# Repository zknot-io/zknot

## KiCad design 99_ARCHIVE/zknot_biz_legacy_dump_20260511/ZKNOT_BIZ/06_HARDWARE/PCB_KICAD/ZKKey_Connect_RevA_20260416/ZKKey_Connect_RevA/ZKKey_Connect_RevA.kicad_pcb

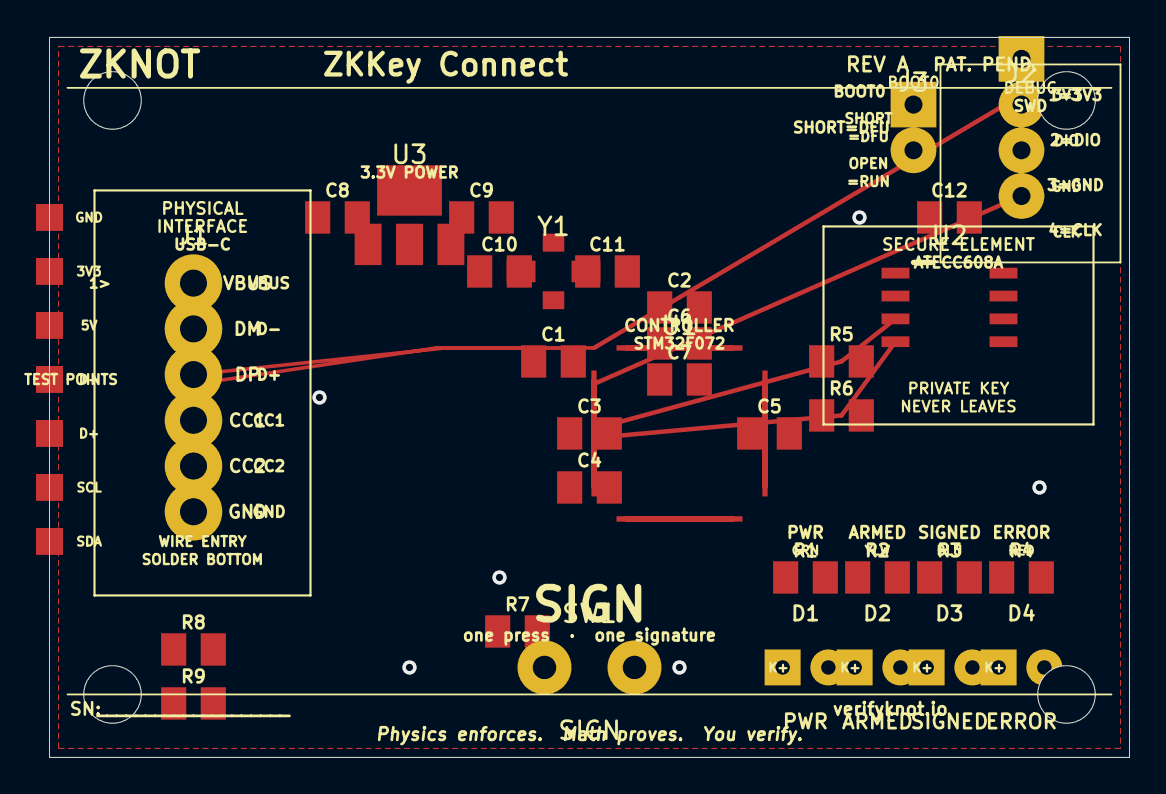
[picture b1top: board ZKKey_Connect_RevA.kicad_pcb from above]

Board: 2 copper layers, 60.0 x 40.0 mm, 33 parts (0 on the bottom side), 19 nets.

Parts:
C1, C2, C3, C4, C5, C6, C7, C8, C9, C10, C11, C12: C_0805_2012Metric
D1: PWR; LED_D3.0mm
D2: ARMED; LED_D3.0mm
D3: SIGNED; LED_D3.0mm
D4: ERROR; LED_D3.0mm
J1: USB-C_Male_Pigtail; PinHeader_1x06_P2.54mm_Vertical
J2: SWD; PinHeader_1x04_P2.54mm_Vertical
J3: BOOT0; PinHeader_1x02_P2.54mm_Vertical
R1, R2, R3, R4, R5, R6, R7, R8, R9: R_0805_2012Metric
SW1: SIGN; SW_Tactile_SPST_Angled_PTS645
U1: STM32F072CBT6; LQFP-48_7x7mm_P0.5mm
U2: ATECC608A; SOIC-8_3.9x4.9mm_P1.27mm
U3: AMS1117-3.3; SOT-223-3_TabPin2
Y1: 8MHz; Crystal_SMD_3225-4Pin_3.2x2.5mm

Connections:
+3.3V: C2.1, C3.1, C4.1, C5.1, C6.1, C7.1, C9.1, C12.1, J2.1, J3.2, R5.1, R6.1, U1.1, U1.2, U1.9, U1.24, U1.48, U2.8, U3.2
+5V: C8.1, U3.3
ATEC_ALERT_PA5: U1.5, U1.6, U1.15, U2.2
BOOT0: J3.1, U1.44
BTN_PA0: R7.1, SW1.1, U1.10
CC1_5V1K: J1.4, R8.1
CC2_5V1K: J1.5, R9.1
GND: C1.2, C2.2, C3.2, C4.2, C5.2, C6.2, C7.2, C8.2, C9.2, C10.2, C11.2, C12.2, D1.1, D2.1, D3.1, D4.1, J1.6, J2.3, R7.2, R8.2, R9.2, SW1.2, U1.8, U1.23, U1.47, U2.3, U3.1, Y1.3, Y1.4
I2C_SCL: R5.2, U1.42, U2.7
I2C_SDA: R6.2, U1.43, U2.5
LED_ARMED_PA2: D2.2, R2.1, R2.2, U1.12
LED_ERROR_PA4: D4.2, R4.1, R4.2, U1.14
LED_PWR_PA1: D1.2, R1.1, R1.2, U1.11
LED_SIGNED_PA3: D3.2, R3.1, R3.2, U1.13
NRST: C1.1, U1.7
SWCLK: J2.4, U1.37
SWDIO: J2.2, U1.34
USB_DM: J1.2, U1.32
USB_DP: J1.3, U1.33

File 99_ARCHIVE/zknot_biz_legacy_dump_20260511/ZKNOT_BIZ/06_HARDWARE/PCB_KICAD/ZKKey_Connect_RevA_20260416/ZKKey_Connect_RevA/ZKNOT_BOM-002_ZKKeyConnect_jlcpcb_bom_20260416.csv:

Comment,Designator,Footprint,LCSC Part #,Qty,Assembly,Notes
STM32F072CBT6,U1,Package_QFP:LQFP-48_7x7mm_P0.5mm,C81720,1,SMT,Reflow — core MCU native USB
ATECC608A-MAHDA-T,U2,Package_SO:SOIC-8_3.9x4.9mm_P1.27mm,C3395330,1,SMT,Reflow — secure element
AMS1117-3.3,U3,Package_TO_SOT_SMD:SOT-223-3_TabPin2,C6186,1,SMT,Reflow — 3.3V LDO
Crystal 8MHz,Y1,Crystal:Crystal_SMD_3225-4Pin_3.2x2.5mm,C9002,1,SMT,Reflow — HSE oscillator
100nF 0805,C1 C3 C4 C5 C12,Capacitor_SMD:C_0805_2012Metric,C49678,5,SMT,Decoupling — NRST/VDD/VDD_USB/ATECC
10uF 0805,C2 C8 C9,Capacitor_SMD:C_0805_2012Metric,C17024,3,SMT,Bulk decoupling — VDD/LDO in/LDO out
1uF 0805,C6,Capacitor_SMD:C_0805_2012Metric,C15849,1,SMT,VDDA bulk
10nF 0805,C7,Capacitor_SMD:C_0805_2012Metric,C57112,1,SMT,VDDA HF
12pF 0805,C10 C11,Capacitor_SMD:C_0805_2012Metric,C1557,2,SMT,Crystal load caps — verify against Y1 datasheet
270R 0805,R1 R2 R3 R4,Resistor_SMD:R_0805_2012Metric,C17630,4,SMT,LED current limit — (3.3V-2.0V)/270=4.8mA
4.7k 0805,R5 R6,Resistor_SMD:R_0805_2012Metric,C23162,2,SMT,I2C pull-ups SCL/SDA
10k 0805,R7,Resistor_SMD:R_0805_2012Metric,C17414,1,SMT,Button pull-down PA0
5.1k 0805,R8 R9,Resistor_SMD:R_0805_2012Metric,C23186,2,SMT,USB-C CC1/CC2 pull-downs — UFP identification
LED 3mm Green,D1,LED_THT:LED_D3.0mm,,1,THT,PWR indicator — source locally
LED 3mm Yellow,D2,LED_THT:LED_D3.0mm,,1,THT,ARMED indicator — source locally
LED 3mm Blue,D3,LED_THT:LED_D3.0mm,,1,THT,SIGNED indicator — source locally
LED 3mm Red,D4,LED_THT:LED_D3.0mm,,1,THT,ERROR indicator — source locally
Tactile Switch 6x6mm,SW1,Button_Switch_THT:SW_Tactile_SPST_Angled_PTS645,,1,THT,SIGN button — source locally PTS645SK43SMTR92LFS or equiv
PinHeader 1x04 2.54mm,J2,Connector_PinHeader_2.54mm:PinHeader_1x04_P2.54mm_Vertical,,1,THT,SWD debug — source locally
PinHeader 1x02 2.54mm,J3,Connector_PinHeader_2.54mm:PinHeader_1x02_P2.54mm_Vertical,,1,THT,BOOT0 jumper — source locally
Jumper shunt 2.54mm,J3_shunt,,,,THT,BOOT0 jumper shunt — keep one on board
USB-C Male Pigtail 5-wire,J1,Connector_PinHeader_2.54mm:PinHeader_1x06_P2.54mm_Vertical,,1,THT,Source: Adafruit 4831 or equiv — VBUS DM DP CC1 CC2 GND — wire through THT holes flood solder bottom
M3 Standoff Nylon 10mm,H1 H2 H3 H4,MountingHole:MountingHole_3.2mm_M3,,4,THT,Optional — for enclosure / bench mounting

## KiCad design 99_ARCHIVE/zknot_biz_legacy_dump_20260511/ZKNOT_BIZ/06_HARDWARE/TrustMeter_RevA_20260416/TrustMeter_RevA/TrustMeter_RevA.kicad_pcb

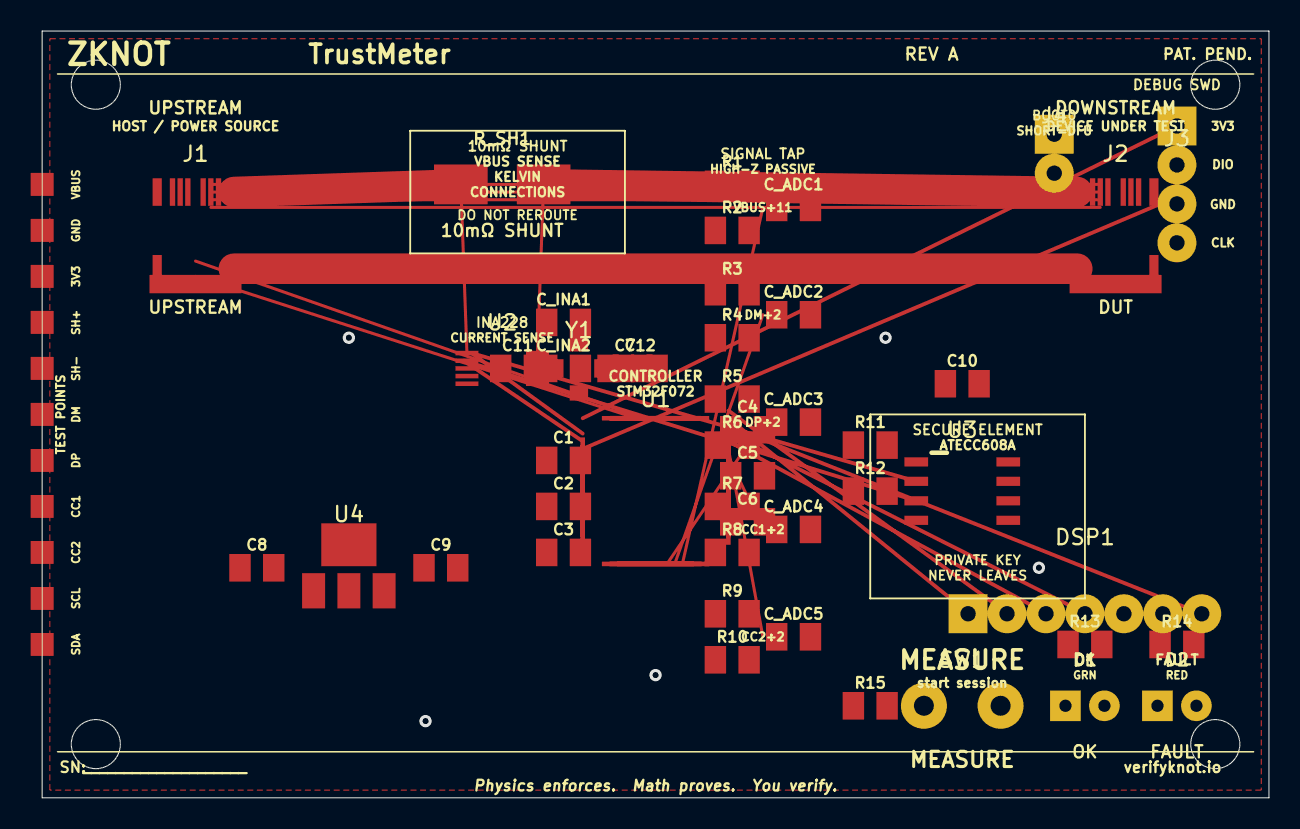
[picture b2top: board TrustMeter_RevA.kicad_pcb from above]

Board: 2 copper layers, 80.0 x 50.0 mm, 48 parts (0 on the bottom side), 31 nets.

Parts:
C1, C2, C3, C4, C5, C6, C7, C8, C9, C10, C11, C12: C_0805_2012Metric
C_ADC1, C_ADC2, C_ADC3, C_ADC4, C_ADC5: C_0805_2012Metric
C_INA1, C_INA2: C_0805_2012Metric
D1: OK; LED_D3.0mm
D2: FAULT; LED_D3.0mm
DSP1: OLED; PinHeader_1x07_P2.54mm_Vertical
J1: UPSTREAM; USB_C_Receptacle_GCT_USB4105-GF-A
J2: DUT; USB_C_Receptacle_GCT_USB4105-GF-A
J3: PinHeader_1x04_P2.54mm_Vertical
J4: PinHeader_1x02_P2.54mm_Vertical
R1, R2, R3, R4, R5, R6, R7, R8, R9, R10, R11, R12, R13, R14, R15: R_0805_2012Metric
R_SH1: 10mΩ SHUNT; R_2512_6332Metric
SW1: MEASURE; SW_Tactile_SPST_Angled_PTS645
U1: STM32F072CBT6; LQFP-48_7x7mm_P0.5mm
U2: INA228; VSSOP-10_3x3mm_P0.5mm
U3: ATECC608A; SOIC-8_3.9x4.9mm_P1.27mm
U4: AMS1117-3.3; SOT-223-3_TabPin2
Y1: Crystal_SMD_3225-4Pin_3.2x2.5mm

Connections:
+3.3V: C1.1, C2.1, C3.1, C4.1, C5.1, C6.1, C9.1, C10.1, DSP1.2, J3.1, J4.2, R11.1, R12.1, U1.1, U1.2, U1.9, U1.24, U1.48, U3.8, U4.2
+5V_VBUS_UP: J1.A4, J1.B4
ADC_CC1: C_ADC4.1, R7.2, R8.1, U1.13
ADC_CC2: C_ADC5.1, R9.2, R10.1, U1.16
ADC_DM: C_ADC2.1, R3.2, R4.1, U1.11
ADC_DP: C_ADC3.1, R5.2, R6.1, U1.12
ADC_VBUS: C_ADC1.1, R1.2, R2.1, U1.10
ATEC_ALERT: U1.39, U3.2
BOOT0: J4.1, U1.44
BTN_MEAS: R15.1, SW1.1, U1.30
CC1_UP: J1.A5, R7.1
CC2_UP: J1.B5, R9.1
DM_UP: J1.A7, R3.1
DP_UP: J1.A6, R5.1
GND: C1.2, C2.2, C3.2, C4.2, C5.2, C6.2, C7.2, C8.2, C9.2, C10.2, C11.2, C12.2, C_ADC1.2, C_ADC2.2, C_ADC3.2, C_ADC4.2, C_ADC5.2, C_INA1.2, C_INA2.2, D1.1, D2.1, DSP1.1, J1.A1, J1.B1, J1.S1, J2.A1, J2.B1, J2.S1, J3.3, R2.2, R4.2, R6.2, R8.2, R10.2, R15.2, SW1.2, U1.8, U1.23, U1.47, U2.3, U2.4, U2.5, U3.3, U4.1, Y1.3, Y1.4
I2C_SCL: R11.2, U1.42, U2.9, U3.7
I2C_SDA: R12.2, U1.43, U2.8, U3.5
INA_ALERT: U1.29, U2.7
LED_FAULT: D2.2, R14.1, R14.2, U1.22
LED_OK: D1.2, R13.1, R13.2, U1.21
NRST: C7.1, U1.7
OLED_CS: DSP1.7, U1.14
OLED_DC: DSP1.6, U1.26
OLED_RST: DSP1.5, U1.27
SPI_MOSI: DSP1.4, U1.17
SPI_SCK: DSP1.3, U1.15
SWCLK: J3.4, U1.37
SWDIO: J3.2, U1.34
VBUS_DOWN: J2.A4, J2.B4
VBUS_SHUNT_HI: R_SH1.1, U2.1
VBUS_SHUNT_LO: C8.1, C_INA1.1, C_INA2.1, R1.1, R_SH1.2, U2.2, U2.6, U2.10, U4.3

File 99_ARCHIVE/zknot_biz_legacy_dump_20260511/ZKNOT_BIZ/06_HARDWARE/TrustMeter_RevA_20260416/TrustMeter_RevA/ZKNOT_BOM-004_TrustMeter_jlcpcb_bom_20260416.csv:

Comment,Designator,Footprint,LCSC Part #,Qty,Assembly,Notes
STM32F072CBT6,U1,Package_QFP:LQFP-48_7x7mm_P0.5mm,C81720,1,SMT,Reflow — same as Connect/Air
INA228AIDGST,U2,Package_SO:VSSOP-10_3x3mm_P0.5mm,C2678360,1,SMT,Reflow — 16-bit current/voltage/power monitor I2C addr 0x40
ATECC608A-MAHDA-T,U3,Package_SO:SOIC-8_3.9x4.9mm_P1.27mm,C3395330,1,SMT,Reflow — secure element signs attestation records
AMS1117-3.3,U4,Package_TO_SOT_SMD:SOT-223-3_TabPin2,C6186,1,SMT,Reflow — 3.3V LDO from VBUS
Crystal 8MHz,Y1,Crystal:Crystal_SMD_3225-4Pin_3.2x2.5mm,C9002,1,SMT,HSE oscillator
10mΩ 1% 2W 2512,R_SH1,Resistor_SMD:R_2512_6332Metric,C17329,1,SMT,SHUNT — Kelvin connections to INA228 IN+/IN- — DO NOT SUBSTITUTE
100k 0805,R1 R3 R4 R5 R6 R7 R8 R9 R10,Resistor_SMD:R_0805_2012Metric,C17407,9,SMT,Voltage divider top+bottom for DM/DP/CC1/CC2 + VBUS top
10k 0805,R2 R15,Resistor_SMD:R_0805_2012Metric,C17414,2,SMT,VBUS divider bottom + button pull-down
4.7k 0805,R11 R12,Resistor_SMD:R_0805_2012Metric,C23162,2,SMT,I2C pull-ups SCL/SDA (shared bus INA228+ATECC)
270R 0805,R13 R14,Resistor_SMD:R_0805_2012Metric,C17630,2,SMT,LED current limit
100nF 0805,C1 C2 C4 C7 C10 C_INA1,Capacitor_SMD:C_0805_2012Metric,C49678,6,SMT,Decoupling
10uF 0805,C3 C8 C9 C_INA2,Capacitor_SMD:C_0805_2012Metric,C17024,4,SMT,Bulk decoupling LDO and INA228 VS
1uF 0805,C5,Capacitor_SMD:C_0805_2012Metric,C15849,1,SMT,VDDA bulk
10nF 0805,C6 C_ADC1 C_ADC2 C_ADC3 C_ADC4 C_ADC5,Capacitor_SMD:C_0805_2012Metric,C57112,6,SMT,VDDA HF + ADC input RC filters
12pF 0805,C11 C12,Capacitor_SMD:C_0805_2012Metric,C1557,2,SMT,Crystal load caps
USB-C Receptacle SMD GCT USB4105-GF-A,J1 J2,Connector_USB:USB_C_Receptacle_GCT_USB4105-GF-A,C2765186,2,SMT,Both connectors same part — J1=upstream J2=DUT
SSD1306 128x64 OLED SPI 0.96in,DSP1,Connector_PinHeader_2.54mm:PinHeader_1x07_P2.54mm_Vertical,,1,THT,Source: AliExpress 0.96" SSD1306 SPI OLED 7-pin — GND VCC CLK MOSI RES DC CS
LED 3mm Green,D1,LED_THT:LED_D3.0mm,,1,THT,OK/NORMAL indicator
LED 3mm Red,D2,LED_THT:LED_D3.0mm,,1,THT,FAULT/HIGH_RISK indicator
Tactile Switch 6x6mm,SW1,Button_Switch_THT:SW_Tactile_SPST_Angled_PTS645,,1,THT,MEASURE button
PinHeader 1x04 2.54mm,J3,Connector_PinHeader_2.54mm:PinHeader_1x04_P2.54mm_Vertical,,1,THT,SWD debug header
PinHeader 1x02 2.54mm,J4,Connector_PinHeader_2.54mm:PinHeader_1x02_P2.54mm_Vertical,,1,THT,BOOT0 jumper
Jumper shunt 2.54mm,J4_shunt,,,,THT,BOOT0 shunt — keep one on board
M3 Standoff Nylon,H1 H2 H3 H4,MountingHole:MountingHole_3.2mm_M3,,4,THT,Enclosure mounting

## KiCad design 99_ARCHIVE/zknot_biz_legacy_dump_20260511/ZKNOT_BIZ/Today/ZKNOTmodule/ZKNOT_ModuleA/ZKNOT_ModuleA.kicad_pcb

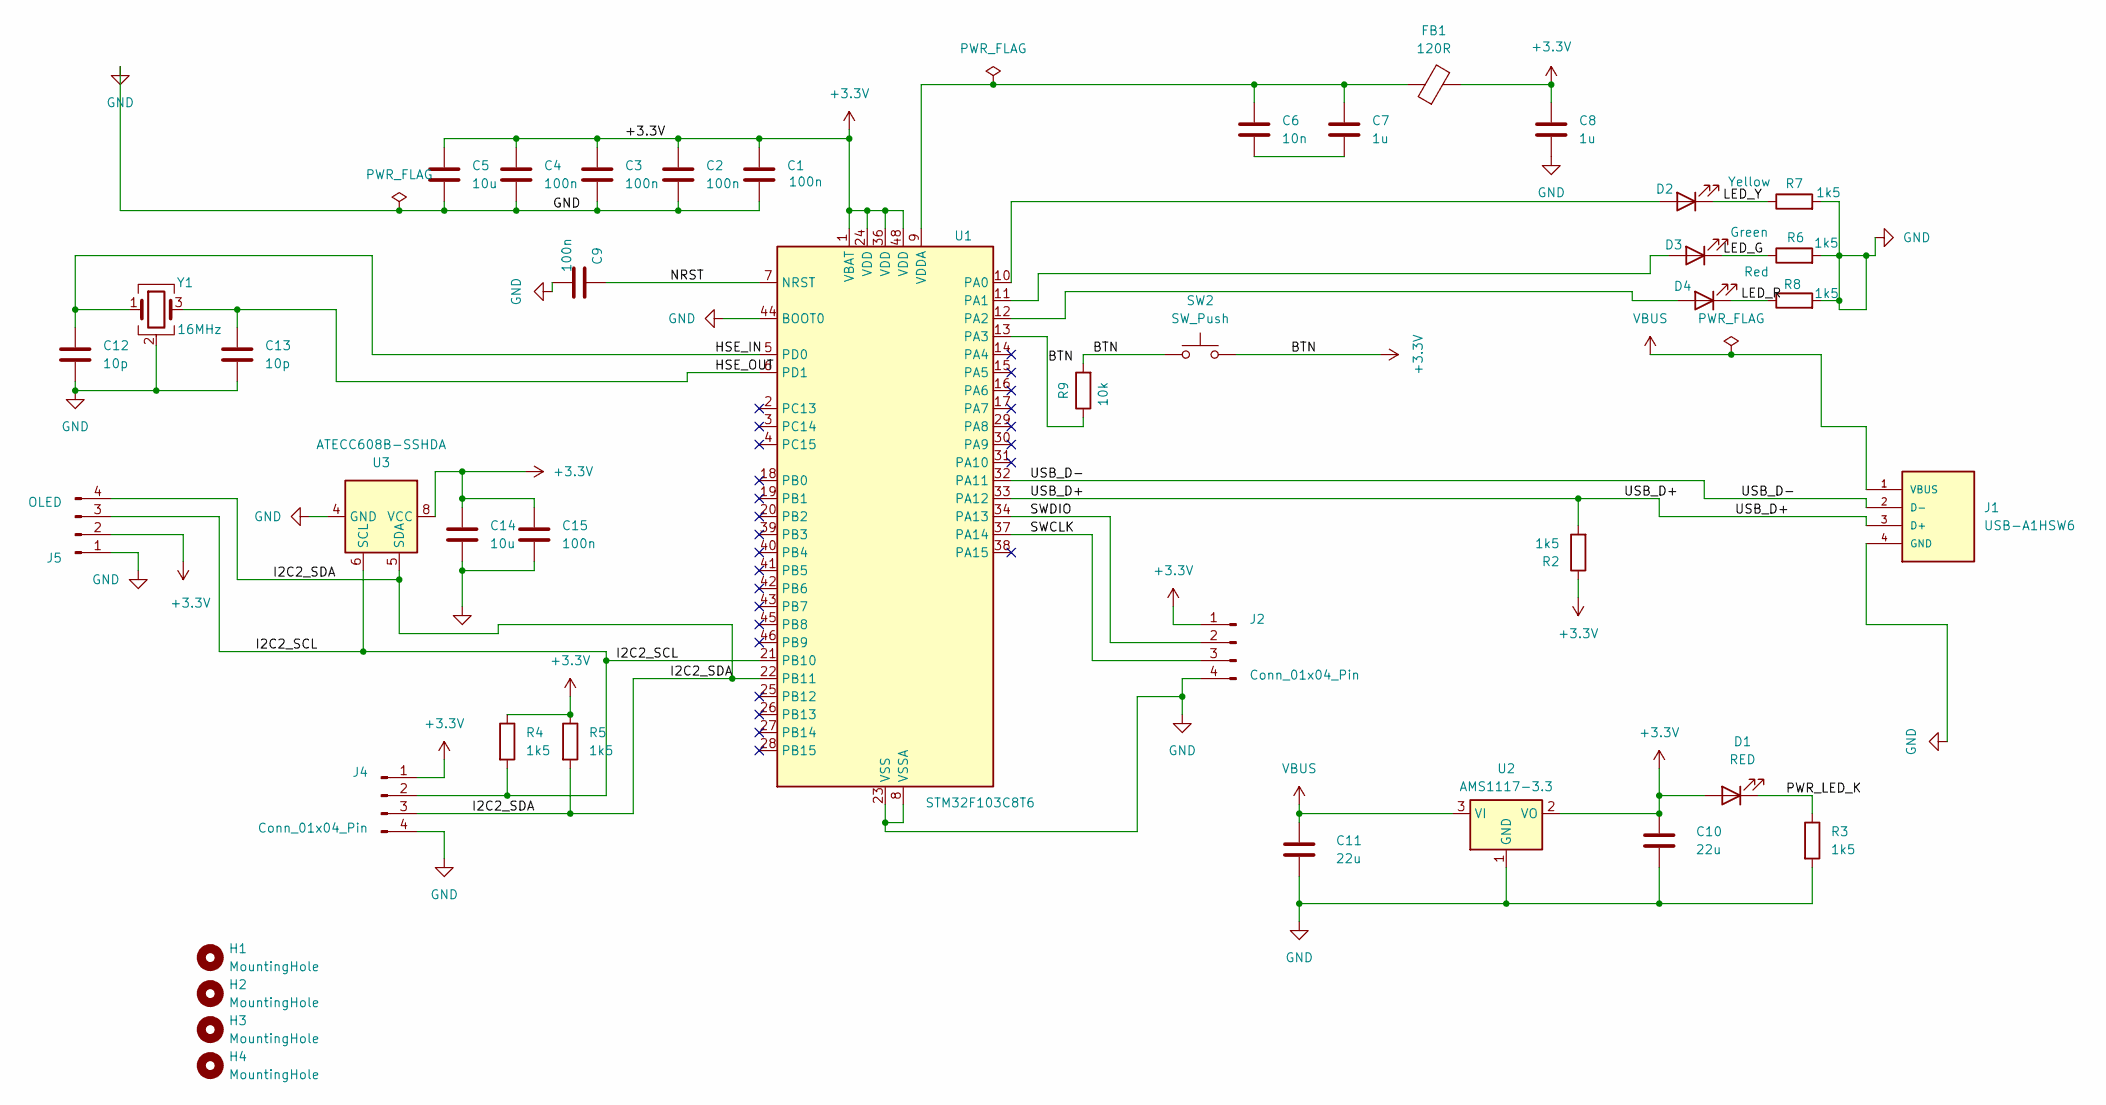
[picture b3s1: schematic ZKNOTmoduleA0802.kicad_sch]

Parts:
C1, C2, C3, C4, C9, C15: 100n; C_0805_2012Metric
C5, C14: 10u; C_0805_2012Metric
C6: 10n; C_0805_2012Metric
C7, C8: 1u; C_0805_2012Metric
C10, C11: 22u; C_0805_2012Metric
C12, C13: 10p; C_0805_2012Metric
D1: RED; LED_0805_2012Metric
D2: Yellow; LED_0805_2012Metric
D3: Green; LED_0805_2012Metric
D4: Red; LED_0805_2012Metric
FB1: 120R; L_0805_2012Metric
H1, H2, H3, H4: MountingHole; MountingHole_2.2mm_M2
J1: USB-A1HSW6; OST_USB-A1HSW6; PARTREV A; DigiKey_Part_Number ED2989-ND
J2, J4: Conn_01x04_Pin; PinHeader_1x04_P2.54mm_Vertical
J5: OLED; PinHeader_1x04_P2.54mm_Vertical
R2, R3, R4, R5, R6, R7, R8: 1k5; R_0805_2012Metric
R9: 10k; R_0805_2012Metric
SW2: SW_Push; SW_SPST_TL3342
U1: STM32F103C8T6; LQFP-48_7x7mm_P0.5mm
U2: AMS1117-3.3; SOT-223-3_TabPin2
U3: ATECC608B-SSHDA; SOIC-8_3.9x4.9mm_P1.27mm
Y1: 16MHz; Crystal_SMD_3225-4Pin_3.2x2.5mm

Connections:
+3.3V: C1.1, C2.1, C3.1, C4.1, C5.1, C8.1, C10.1, C14.1, C15.1, D1.2 (A), FB1.2, J2.1, J4.1, J5.2, R2.1, R4.1, R5.1, R9.1, R9.2, SW2.1, SW2.2, U1.1 (VBAT), U1.13 (PA3), U1.24 (VDD), U1.36 (VDD), U1.48 (VDD), U2.2 (VO), U3.8 (VCC)
/HSE_IN: C12.1, U1.5 (PD0), Y1.1
/HSE_OUT: C13.1, U1.6 (PD1), Y1.3
/I2C2_SCL: J4.2, J5.3, R4.2, U1.21 (PB10), U3.6 (SCL)
/I2C2_SDA: J4.3, J5.4, R5.2, U1.22 (PB11), U3.5 (SDA)
/LED_G: D3.1 (K), R6.1
/LED_R: D4.1 (K), R8.1
/LED_Y: D2.1 (K), R7.1
/NRST: C9.1, U1.7 (NRST)
/PWR_LED_K: D1.1 (K), R3.1
/SWCLK: J2.3, U1.37 (PA14)
/SWDIO: J2.2, U1.34 (PA13)
/USB_D+: J1.3 (D+), R2.2, U1.33 (PA12)
/USB_D-: J1.2 (D-), U1.32 (PA11)
GND: C1.2, C2.2, C3.2, C4.2, C5.2, C8.2, C9.2, C10.2, C11.2, C12.2, C13.2, C14.2, C15.2, J1.4 (GND), J2.4, J4.4, J5.1, R3.2, R6.2, R7.2, R8.2, U1.8 (VSSA), U1.23 (VSS), U1.35 (VSS), U1.44 (BOOT0), U1.47 (VSS), U2.1 (GND), U3.4 (GND), Y1.2 (G), Y1.4 (G)
unnamed: C6.2, C7.2
unnamed: D2.2 (A), U1.10 (PA0)
unnamed: D3.2 (A), U1.11 (PA1)
unnamed: D4.2 (A), U1.12 (PA2)
unnamed: C6.1, C7.1, FB1.1, U1.9 (VDDA)
VBUS: C11.1, J1.1 (VBUS), U2.3 (VI)

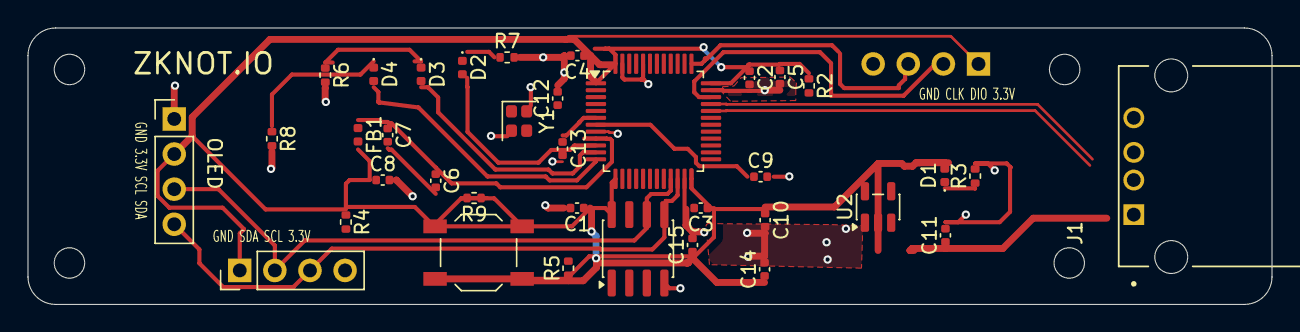
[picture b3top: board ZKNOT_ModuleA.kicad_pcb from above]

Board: 2 copper layers, 90.0 x 20.0 mm, 41 parts (1 on the bottom side), 21 nets.

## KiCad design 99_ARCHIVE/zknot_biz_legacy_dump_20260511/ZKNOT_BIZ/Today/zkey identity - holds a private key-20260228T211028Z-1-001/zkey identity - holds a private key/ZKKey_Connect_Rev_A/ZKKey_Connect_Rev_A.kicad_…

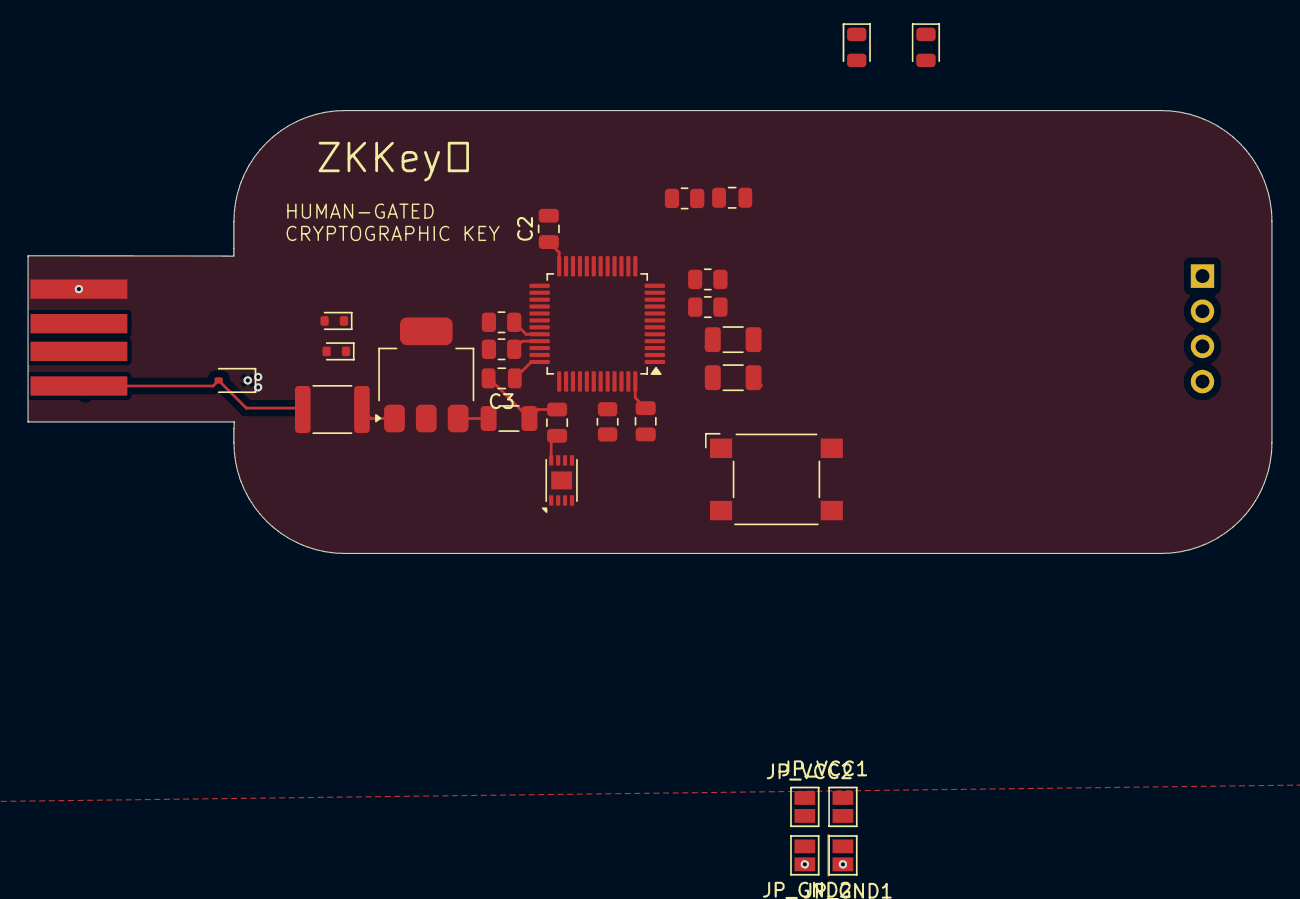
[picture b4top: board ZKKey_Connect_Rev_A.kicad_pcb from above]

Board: 2 copper layers, 89.9 x 32.0 mm, 30 parts (1 on the bottom side), 19 nets.

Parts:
C1, C7, C8: 4.7-10uF; C_1206_3216Metric
C2, C3, C4, C5: .1uF; C_0805_2012Metric
C6: 100nF; C_0805_2012Metric
D1, D2: LED; LED_0805_2012Metric
D3: PTVS5V0Z1USK; D_SOD-323
D4, D5: ESD5Zxx; D_SOD-523
F1: Polyfuse; Fuse_1812_4532Metric
J1: Conn_01x01_Pin; USB_A_PowerVerify_4Pin_2.4mm
J2: Conn_01x04_Pin; PinHeader_1x04_P2.54mm_Horizontal
JP1: JP_VCC1; SolderJumper-2_P1.3mm_Open_Pad1.0x1.5mm
JP2: JP_VCC2; SolderJumper-2_P1.3mm_Open_Pad1.0x1.5mm
JP3: JP_GND1; SolderJumper-2_P1.3mm_Open_Pad1.0x1.5mm
JP4: JP_GND2; SolderJumper-2_P1.3mm_Open_Pad1.0x1.5mm
R1, R2: 330-1k; R_0805_2012Metric
R3: 10k; R_0805_2012Metric
R4: 100k; R_0805_2012Metric
R5, R6: 22; R_0805_2012Metric
SW1: SW_Push; SW_SPST_Omron_B3FS-100xP
U1: ATECC608A-MAHDA; DFN-8-1EP_3x2mm_P0.5mm_EP1.3x1.5mm
U2: STM32F103CBTx; LQFP-48_7x7mm_P0.5mm
U3: SPX2920M3-3.3_SOT223; SOT-223-3_TabPin2

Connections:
/+3.3V: C1.1, C1.2, C2.1, C2.2, C3.1, C3.2, C4.1, C4.2, C5.1, C5.2, C6.1, F1.2, JP1.1 (A), JP2.1 (A), R3.2, SW1.2, U1.8 (VCC), U2.24 (VDD), U2.36 (VDD), U2.48 (VDD), U3.1 (VI), U3.3 (VO)
/OLED_PIN1: J2.OLED_PIN1 (Pin_1), JP1.2 (B), JP2.2 (B)
/OLED_PIN2: J2.OLED_PIN2 (Pin_2), JP3.2 (B), JP4.2 (B)
/OLED_SCL: C7.2, J2.OLED_SCL (Pin_3)
/OLED_SDA: C7.1, C8.1, C8.2, J2.OLED_SDA (Pin_4), U1.5 (SDA), U2.43 (PB7)
/USB_DM: D5.1 (K), J1.2, R5.2
/USB_DP: D4.1 (K), J1.3, R6.2
/VBUS_RAW: D3.2 (A), F1.1, J1.1
GND: C6.2, D1.1 (K), D2.1 (K), D3.1 (K), J1.4, JP3.1 (A), JP4.1 (A), R4.2, U1.4 (GND), U1.9 (EP), U2.23 (VSS), U2.35 (VSS), U2.47 (VSS), U3.2 (GND)
unnamed: D1.2 (A), R1.2
unnamed: D2.2 (A), R2.2
unnamed: U1.6 (SCL), U2.42 (PB6)
unnamed: R4.1, U2.44 (BOOT0)
unnamed: R3.1, U2.7 (NRST)
unnamed: SW1.1, U2.10 (PA0)
unnamed: R1.1, U2.11 (PA1)
unnamed: R2.1, U2.12 (PA2)
unnamed: R6.1, U2.32 (PA11)
unnamed: R5.1, U2.33 (PA12)

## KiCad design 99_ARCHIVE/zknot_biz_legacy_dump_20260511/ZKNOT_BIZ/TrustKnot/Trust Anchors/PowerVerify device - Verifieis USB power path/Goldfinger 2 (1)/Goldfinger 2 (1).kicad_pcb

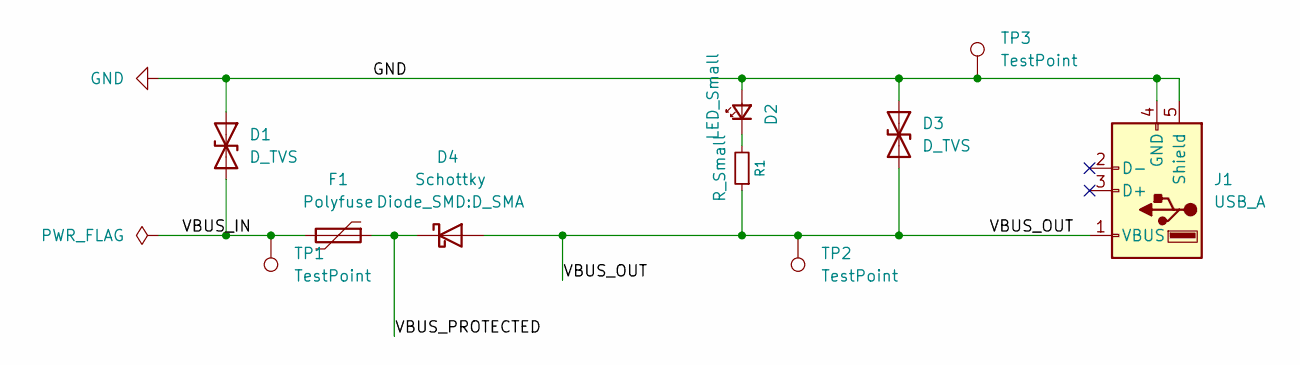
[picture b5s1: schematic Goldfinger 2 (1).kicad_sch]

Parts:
D1, D3: D_TVS; D_SOD-323
D2: LED_Small; LED_0805_2012Metric
D4: Schottky; D_SMA
F1: Polyfuse; Fuse_2920_7451Metric
J1: USB_A; USB_A_Connfly_DS1095
R1: R_Small; R_0805_2012Metric
TP1, TP2, TP3: TestPoint; TestPoint_Pad_D1.5mm

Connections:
/VBUS_IN: D1.2 (A2), F1.2, TP1.1; also elsewhere on the board
/VBUS_OUT: D3.2 (A2), D4.2 (A), J1.1 (VBUS), R1.1, TP2.1
/VBUS_PROTECTED: D4.1 (K), F1.1
GND: D1.1 (A1), D2.2 (A), D3.1 (A1), J1.4 (GND), J1.5 (Shield), TP3.1; also elsewhere on the board
unnamed: D2.1 (K), R1.2

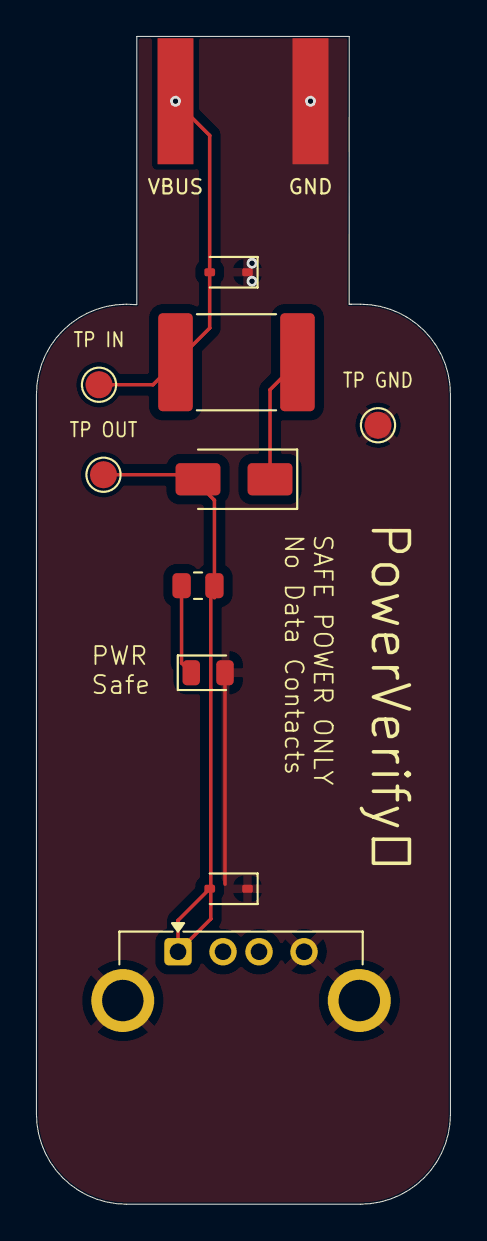
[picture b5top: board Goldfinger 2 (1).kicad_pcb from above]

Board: 2 copper layers, 23.0 x 64.9 mm, 11 parts (0 on the bottom side), 5 nets.

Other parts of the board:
USB_A: USB_A; USB_A_PowerVerify_2Finger_2.4mm_FIXED

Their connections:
/VBUS_IN: USB_A.1 (VBUS); also elsewhere on the board
GND: USB_A.2 (D-); also elsewhere on the board
